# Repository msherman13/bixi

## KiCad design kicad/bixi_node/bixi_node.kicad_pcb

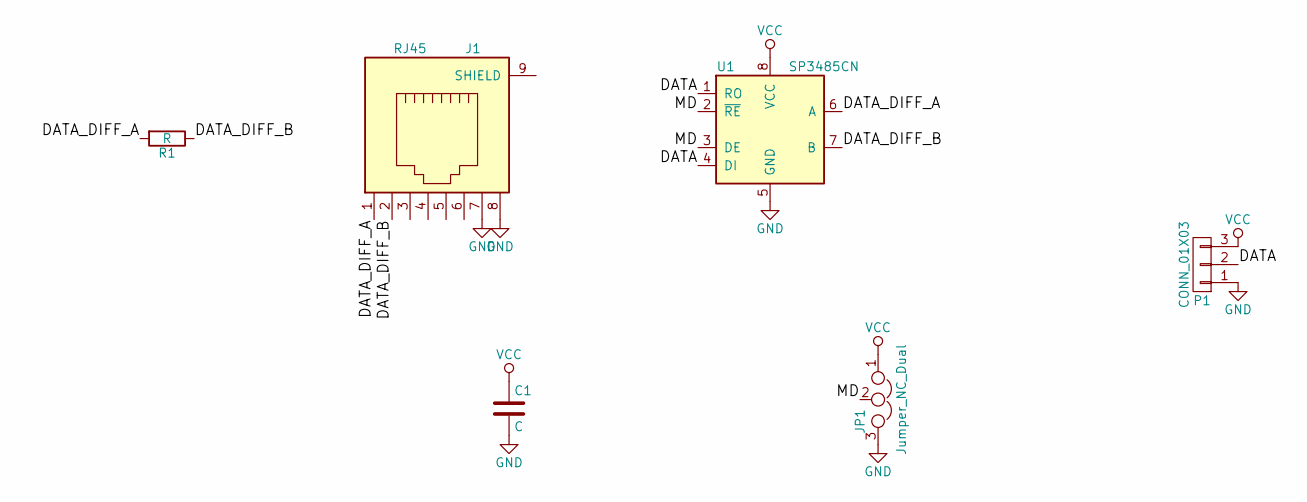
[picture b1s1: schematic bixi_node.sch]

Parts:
C1: C; C_Axial_L3.8mm_D2.6mm_P7.50mm_Horizontal
J1: RJ45; RJ45_8
JP1: Jumper_NC_Dual; jumper_3_pin_fixed
P1: CONN_01X03; 3-wire-hole-with-relief
R1: R; Resistor_Horizontal_RM7mm
U1: SP3485CN; DIP-8_W7.62mm

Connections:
/DATA: P1.2, U1.1 (RO), U1.4 (DI)
/DATA_DIFF_A: J1.1, R1.2, U1.6 (A)
/DATA_DIFF_B: J1.2, R1.1, U1.7 (B)
/MD: JP1.2, U1.2 (~RE~), U1.3 (DE)
GND: C1.2, J1.7, J1.8, JP1.3, P1.1, U1.5 (GND)
VCC: C1.1, JP1.1, P1.3, U1.8 (VCC)

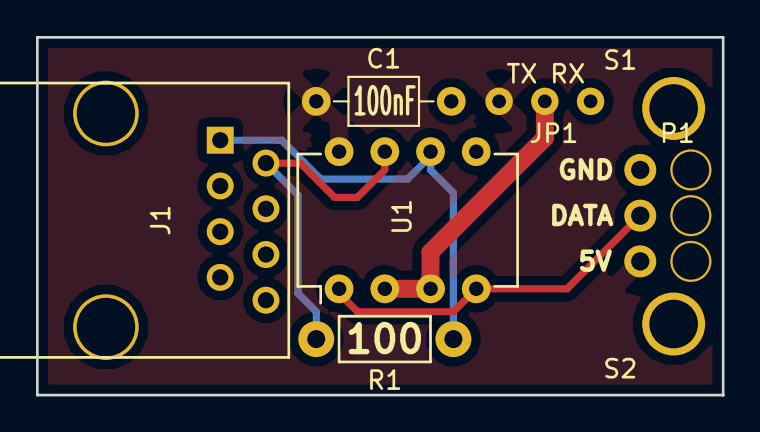
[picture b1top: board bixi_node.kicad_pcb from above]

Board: 2 copper layers, 38.1 x 19.9 mm, 8 parts (0 on the bottom side), 6 nets.

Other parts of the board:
S1, S2: MountingHole_2.7mm_Pad

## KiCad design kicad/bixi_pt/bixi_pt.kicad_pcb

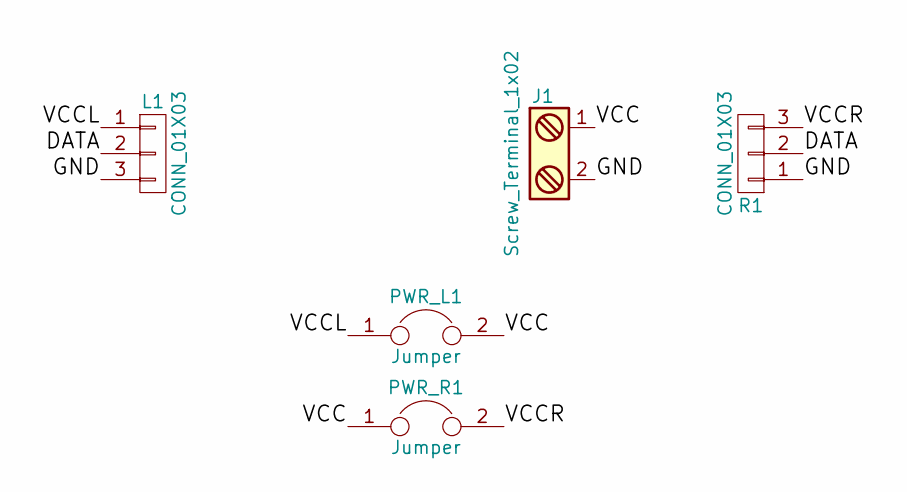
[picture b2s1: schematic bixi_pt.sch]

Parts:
J1: Screw_Terminal_1x02; OSTYK42102030-2P-Terminal
L1: CONN_01X03; 3-wire-hole-with-relief
PWR_L1: Jumper; Pin_Header_Straight_1x02_Pitch2.54mm
PWR_R1: Jumper; Pin_Header_Straight_1x02_Pitch2.54mm
R1: CONN_01X03; 3-wire-hole-with-relief

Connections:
/DATA: L1.2, R1.2
/GND: J1.2, L1.3, R1.1
/VCC: J1.1, PWR_L1.2, PWR_R1.1
/VCCL: L1.1, PWR_L1.1
/VCCR: PWR_R1.2, R1.3

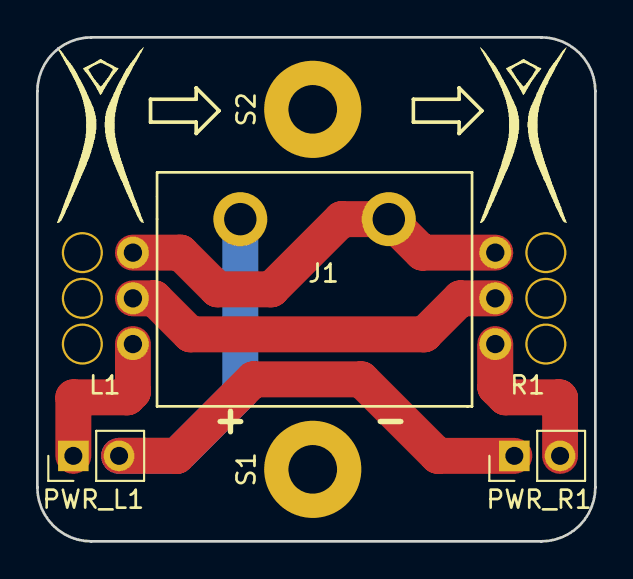
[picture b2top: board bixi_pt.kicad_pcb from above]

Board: 2 copper layers, 31.0 x 28.0 mm, 9 parts (0 on the bottom side), 5 nets.

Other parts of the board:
S1, S2: MountingHole_3.5mm; MountingHole_2.7mm_Pad
burner-logo: burner-logo-fs
burner-logo#2: burner-logo-fs

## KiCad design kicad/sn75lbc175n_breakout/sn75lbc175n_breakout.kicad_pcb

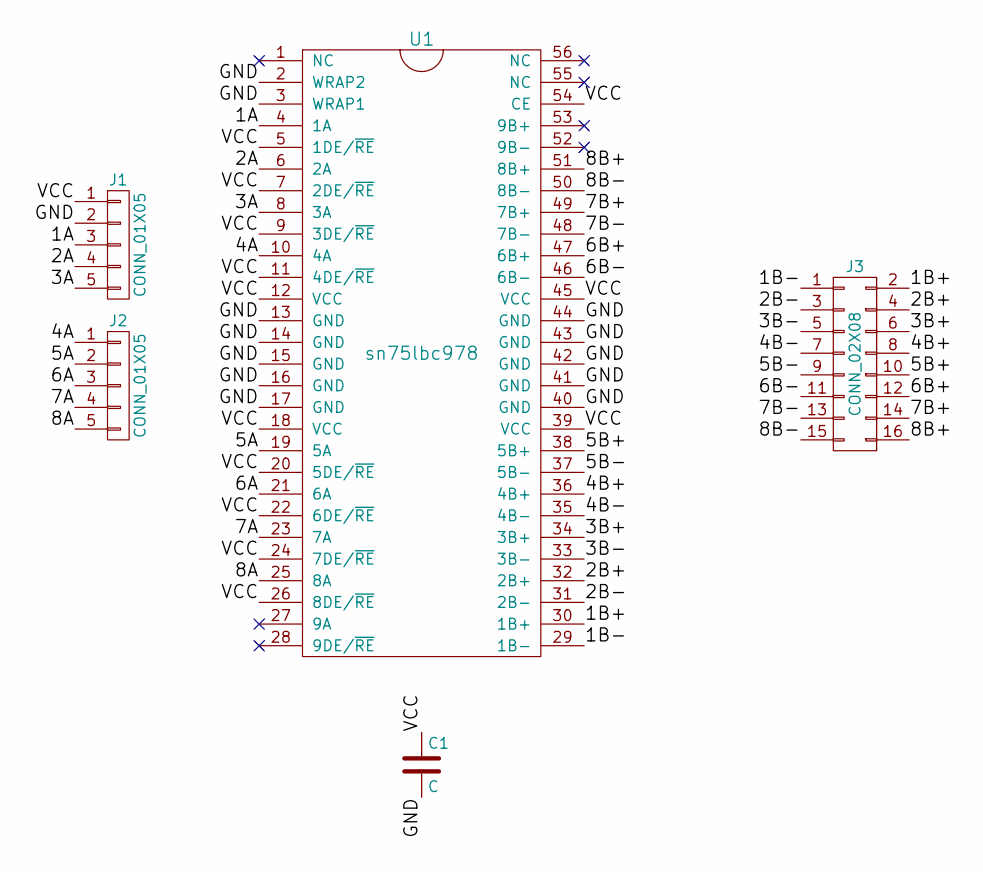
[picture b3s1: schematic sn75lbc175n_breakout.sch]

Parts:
C1: C; C_Disc_D4.7mm_W2.5mm_P5.00mm
J1, J2: CONN_01X05; Pin_Header_Straight_1x05_Pitch2.54mm
J3: CONN_02X08; Pin_Header_Straight_2x08_Pitch2.54mm
U1: sn75lbc978; SSOP-56_7.5x18.5mm_Pitch0.635mm

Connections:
/1A: J1.3, U1.4 (1A)
/1B+: J3.2, U1.30 (1B+)
/1B-: J3.1, U1.29 (1B-)
/2A: J1.4, U1.6 (2A)
/2B+: J3.4, U1.32 (2B+)
/2B-: J3.3, U1.31 (2B-)
/3A: J1.5, U1.8 (3A)
/3B+: J3.6, U1.34 (3B+)
/3B-: J3.5, U1.33 (3B-)
/4A: J2.1, U1.10 (4A)
/4B+: J3.8, U1.36 (4B+)
/4B-: J3.7, U1.35 (4B-)
/5A: J2.2, U1.19 (5A)
/5B+: J3.10, U1.38 (5B+)
/5B-: J3.9, U1.37 (5B-)
/6A: J2.3, U1.21 (6A)
/6B+: J3.12, U1.47 (6B+)
/6B-: J3.11, U1.46 (6B-)
/7A: J2.4, U1.23 (7A)
/7B+: J3.14, U1.49 (7B+)
/7B-: J3.13, U1.48 (7B-)
/8A: J2.5, U1.25 (8A)
/8B+: J3.16, U1.51 (8B+)
/8B-: J3.15, U1.50 (8B-)
/GND: C1.2, J1.2, U1.2 (WRAP2), U1.3 (WRAP1), U1.13 (GND), U1.14 (GND), U1.15 (GND), U1.16 (GND), U1.17 (GND), U1.40 (GND), U1.41 (GND), U1.42 (GND), U1.43 (GND), U1.44 (GND)
/VCC: C1.1, J1.1, U1.5 (1DE/~RE), U1.7 (2DE/~RE), U1.9 (3DE/~RE), U1.11 (4DE/~RE), U1.12 (VCC), U1.18 (VCC), U1.20 (5DE/~RE), U1.22 (6DE/~RE), U1.24 (7DE/~RE), U1.26 (8DE/~RE), U1.39 (VCC), U1.45 (VCC), U1.54 (CE)

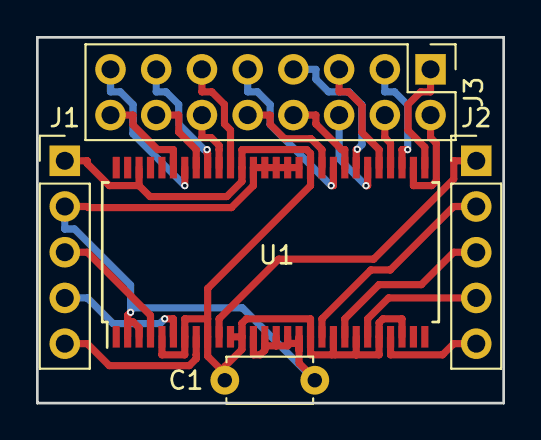
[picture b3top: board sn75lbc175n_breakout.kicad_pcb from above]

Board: 2 copper layers, 25.9 x 20.3 mm, 5 parts (0 on the bottom side), 26 nets.

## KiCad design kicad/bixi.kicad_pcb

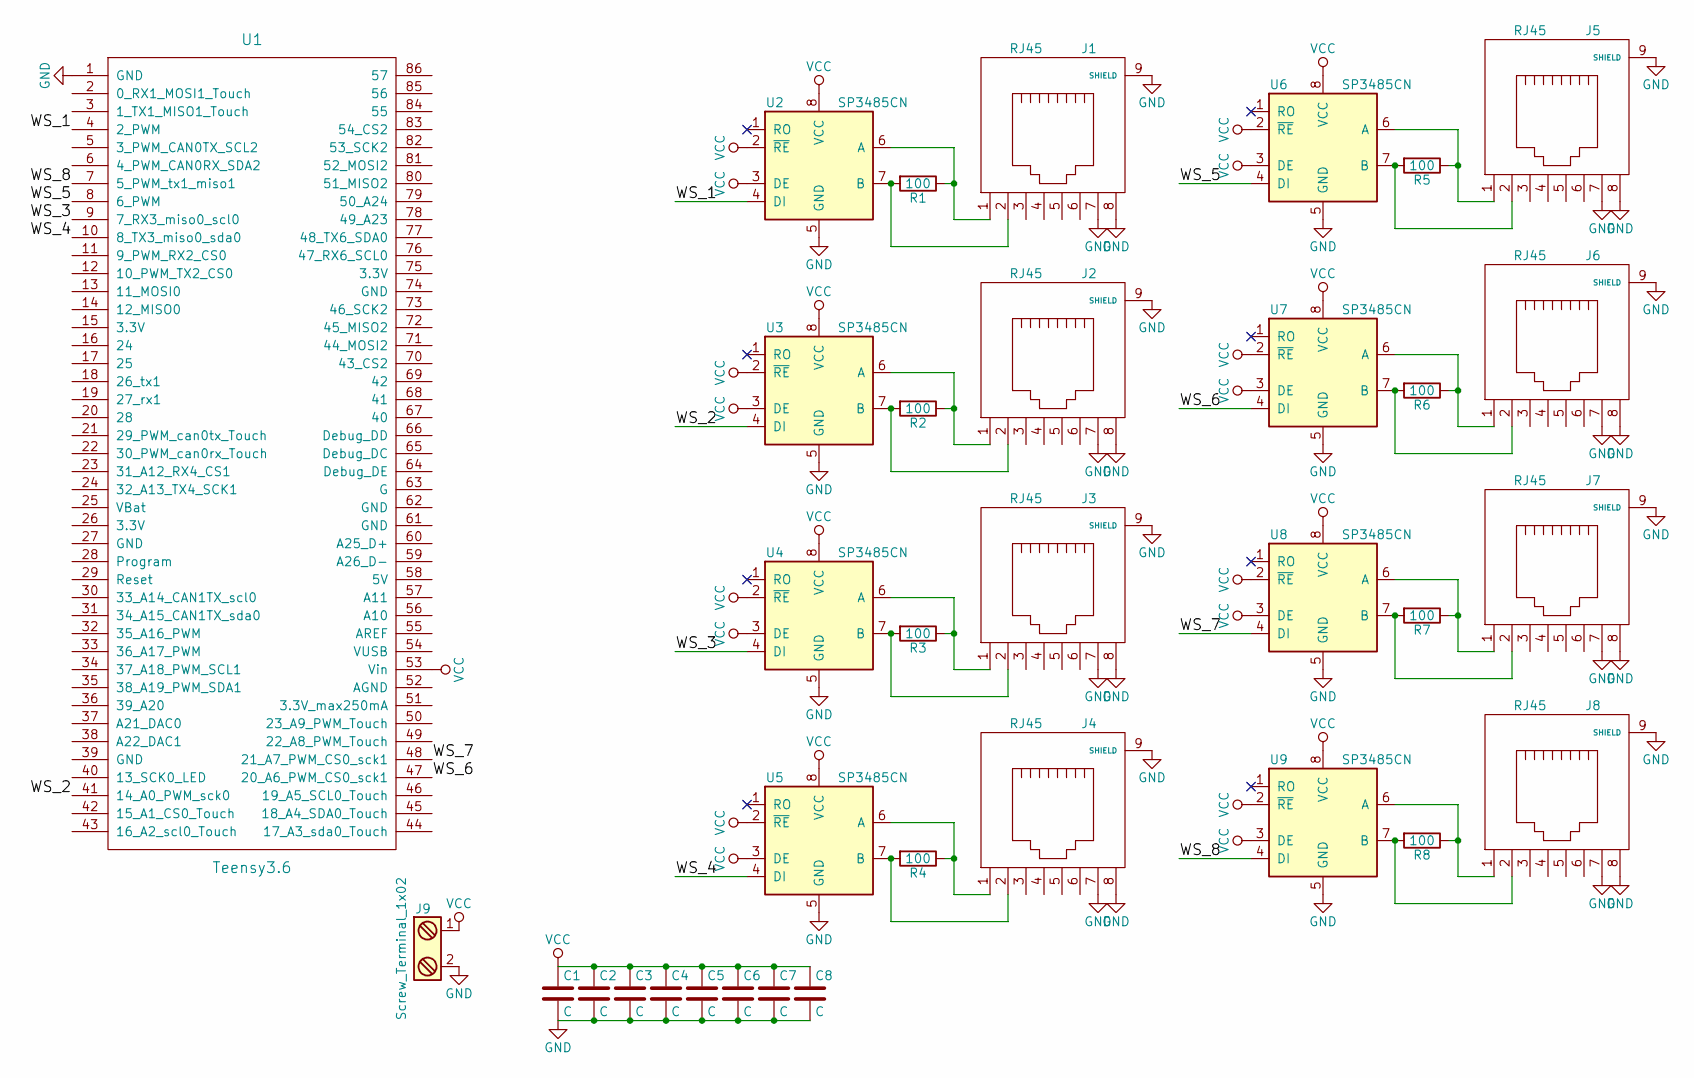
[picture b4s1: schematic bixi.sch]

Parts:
C1, C2, C3, C4, C5, C6, C7, C8: C; C_Disc_D3_P2.5
J1, J2, J3, J4, J5, J6, J7, J8: RJ45; RJ45_8
J9: Screw_Terminal_1x02; HB9500-2P
R1, R2, R3, R4, R5, R6, R7, R8: 100; Resistor_Horizontal_RM7mm
U1: Teensy3.6; Teensy35_36
U2, U3, U4, U5, U6, U7, U8, U9: SP3485CN; DIP-8_W7.62mm

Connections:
/WS_1: U1.4 (2_PWM), U2.4 (DI)
/WS_2: U1.41 (14_A0_PWM_sck0), U3.4 (DI)
/WS_3: U1.9 (7_RX3_miso0_scl0), U4.4 (DI)
/WS_4: U1.10 (8_TX3_miso0_sda0), U5.4 (DI)
/WS_5: U1.8 (6_PWM), U6.4 (DI)
/WS_6: U1.47 (20_A6_PWM_CS0_sck1), U7.4 (DI)
/WS_7: U1.48 (21_A7_PWM_CS0_sck1), U8.4 (DI)
/WS_8: U1.7 (5_PWM_tx1_miso1), U9.4 (DI)
GND: C1.2, C2.2, C3.2, C4.2, C5.2, C6.2, C7.2, C8.2, J1.7, J1.8, J1.9 (SHIELD), J2.7, J2.8, J2.9 (SHIELD), J3.7, J3.8, J3.9 (SHIELD), J4.7, J4.8, J4.9 (SHIELD), J5.7, J5.8, J5.9 (SHIELD), J6.7, J6.8, J6.9 (SHIELD), J7.7, J7.8, J7.9 (SHIELD), J8.7, J8.8, J8.9 (SHIELD), J9.2, U1.1 (GND), U2.5 (GND), U3.5 (GND), U4.5 (GND), U5.5 (GND), U6.5 (GND), U7.5 (GND), U8.5 (GND), U9.5 (GND); also elsewhere on the board
unnamed: J1.1, R1.1, U2.6 (A)
unnamed: J1.2, R1.2, U2.7 (B)
unnamed: J2.1, R2.1, U3.6 (A)
unnamed: J2.2, R2.2, U3.7 (B)
unnamed: J3.1, R3.1, U4.6 (A)
unnamed: J3.2, R3.2, U4.7 (B)
unnamed: J4.1, R4.1, U5.6 (A)
unnamed: J4.2, R4.2, U5.7 (B)
unnamed: J5.1, R5.1, U6.6 (A)
unnamed: J5.2, R5.2, U6.7 (B)
unnamed: J6.1, R6.1, U7.6 (A)
unnamed: J6.2, R6.2, U7.7 (B)
unnamed: J7.1, R7.1, U8.6 (A)
unnamed: J7.2, R7.2, U8.7 (B)
unnamed: J8.1, R8.1, U9.6 (A)
unnamed: J8.2, R8.2, U9.7 (B)
VCC: C1.1, C2.1, C3.1, C4.1, C5.1, C6.1, C7.1, C8.1, J9.1, U1.53 (Vin), U2.2 (~RE~), U2.3 (DE), U2.8 (VCC), U3.2 (~RE~), U3.3 (DE), U3.8 (VCC), U4.2 (~RE~), U4.3 (DE), U4.8 (VCC), U5.2 (~RE~), U5.3 (DE), U5.8 (VCC), U6.2 (~RE~), U6.3 (DE), U6.8 (VCC), U7.2 (~RE~), U7.3 (DE), U7.8 (VCC), U8.2 (~RE~), U8.3 (DE), U8.8 (VCC), U9.2 (~RE~), U9.3 (DE), U9.8 (VCC)

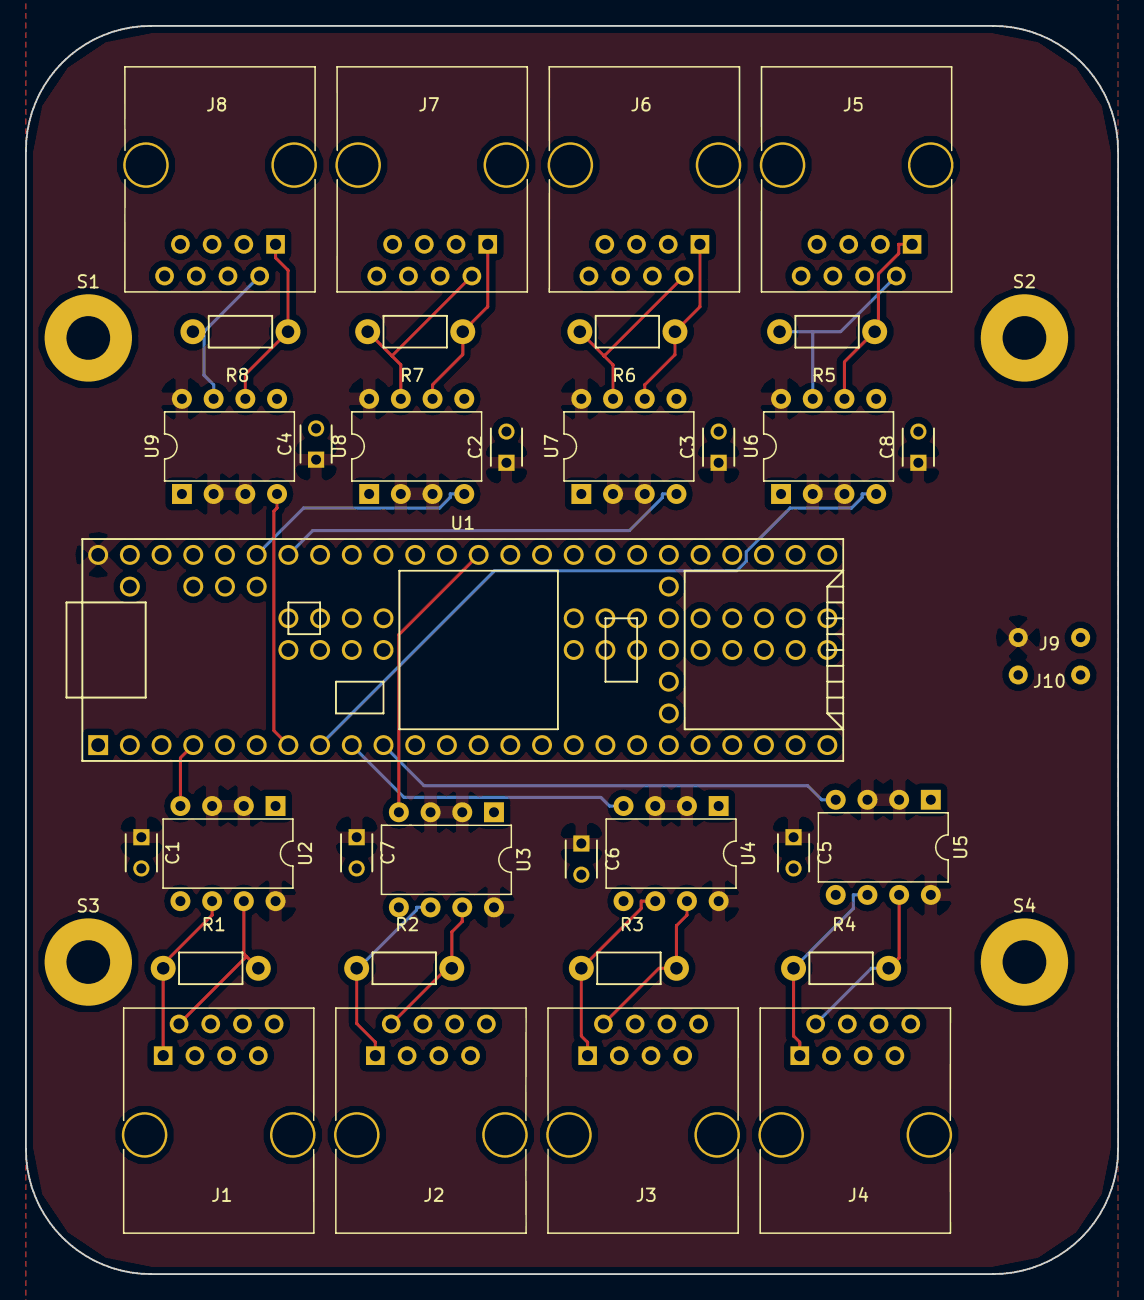
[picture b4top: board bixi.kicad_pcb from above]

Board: 2 copper layers, 87.5 x 100.0 mm, 40 parts (0 on the bottom side), 26 nets.

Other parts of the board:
J10: Screw_Terminal_1x01; A116169CT_SPADE_CONNECTOR
S1, S2, S3, S4: MountingHole_3.5mm_Pad
bm_streets: bm_streets

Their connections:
GND: J10.1; also elsewhere on the board

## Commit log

2017-01-22 makefile, example neopixel driver
2017-02-12 initial routines working. out of memory on arduino nano
2017-03-04 style fixes, fix to HoldRainbow hue wraparound
2017-03-04 support for driving strips on multiple pins
2017-03-04 fixed exitRoutine bug, removed debug logging
2017-03-18 Parallel output via FastLED; RoutineGrow
2017-03-18 initial kicad draft
2017-03-19 kicad schematic and layout
2017-03-19 updated controller layout
2017-03-19 more controller layout changes
2017-03-26 controller and receiver boards almost done for v1
2017-04-02 controller board screw terminal, screw holes. ready for build
2017-04-02 keep-out area for terminal block, finalized node pcb
2017-04-02 larger pads on screw terminal connector
2017-04-09 both pcb's sent to fab
2017-04-09 fix to silkscreen placement on bixi pcb
2017-04-16 bixi dome dimensions image
2017-04-25 v2 pcb
2017-04-29 bixi node updates
2017-04-30 v3 pcb first pass
2017-04-30 ignore swap files
2017-04-30 adding paul's repo as a submodule
2017-04-30 initial work on laying out the LED's on the frame
2017-05-02 v3 boards almost complete. added xcvr breakout, passthrough boards
2017-05-04 v3 pcb's plotted, ready for fab
2017-05-06 indices changes
2017-05-06 midway through addressing layer
2017-05-12 first changes for v4 pcb's
2017-05-12 remove std::string (not supported by arduino)
2017-05-13 initial work on pure c++ version
2017-05-13 sim is functional
2017-05-13 run sim in fake clock domain
2017-05-16 syntax
2017-05-16 move main.cpp into emulator files
2017-05-16 first piece of PixelArray re-write
2017-05-16 FastLED: Fix issue with driver on short strands
2017-05-16 PixelArray takes external array as reference
2017-05-17 plain implementation is functional
2017-05-17 dimensions2, first hex routine
2017-05-19 DoubleHex, bidirectional plains, color pallete
2017-05-20 rgb2hsv conversion for sim is compiling, probably doesnt work
2017-05-20 polygon, routines owned by pixel array
2017-05-20 RoutineGlare
2017-05-20 initial work on routine-sticks
2017-05-21 added missing file
2017-05-21 new power injection board is ready
2017-05-21 new controller board
2017-05-21 fixes to boards, node still in progress
2017-05-21 RoutineSticks, RoutineCrawl working
2017-05-22 CDome, fixes to swipe routine
2017-05-23 updated controller board with stacked rj45
2017-05-23 re-plotted controller board after DRC
2017-05-24 node work for keystone box
2017-05-24 final v4 pcb's, sent to production
2017-05-29 routine fire work
2017-05-29 quickcg skeleton
2017-05-29 some cleanup
2017-06-03 fix a bug introduced in the previous commit
2017-06-03 more bug fixes, fixed memory leak
2017-06-03 Consolidated pixel array constructors, dome mappings
2017-06-03 initial work on routine balls, raster grid
2017-06-03 routine balls is functional
2017-06-04 everything functional, first work on 2d routine
2017-06-04 some changes
2017-06-04 map projections seem to be functional, needs testing
2017-06-04 lambert conformal projection seems functional
2017-06-04 lambert map projection is fully functional
2017-06-04 removed CompleteConfig, kills memory. use external override instead
2017-06-04 move pixelarrays to static memory pool
2017-06-05 fixed the memory allocation nightmare. everything statically allocated
2017-06-06 Split out pixel array with legs to derived class
2017-06-06 shutdown interface in CRoutine, RoutineBall shutdown, NoTech implementation
2017-06-06 fixup of dome for shutdown routine
2017-06-06 fix to dome, routineBall shutdown
2017-06-10 fade-in transitions are functional
2017-06-11 RoutineRain looks good
2017-06-11 fix include in balls
2017-06-11 rough dimensions for dome, generation scripts
2017-06-11 remove debug logging
2017-06-11 checking in
2017-06-11 fixes for refresh rate, addressing issue
2017-06-11 make Dome leg-based
2017-06-11 Dome shape constructors
2017-06-15 everything working except make issue with teensy
2017-06-16 new layout, routine-spin, fixed point math
2017-06-18 fix map corners
2017-06-20 new dimensions from sketchup, mapprojection is broken
2017-06-21 fixed lambert projection (was using std::abs instead of fabs)
2017-06-21 OCTO2813 dma
2017-06-21 routinespin is faster
2017-06-21 octo emulator
2017-06-21 linker
2017-06-21 missing file
2017-06-21 initial version working. need to move map projection to pre-processor
2017-06-22 map projection in pre-processor
2017-06-24 dome and power maps
2017-06-24 dome and power map pdf's
2017-06-24 lots of progress
2017-06-24 transition out instead of transition in
2017-06-24 remove glare from dome for now
2017-06-25 LegsAndNeck is functional
2017-06-25 fixed arduino make
2017-06-25 head is functional
2017-06-25 fire is still kinda broken`
2017-06-27 some work on color correction
2017-07-15 add 3 led's to every dome dimension
2017-07-19 bug fix in 3d_locations_from_sketchup file
2017-07-19 turn off gamma correction, fix issue with uninitialized CRGB values
2017-07-20 fix a bug which allows Dome to go into RoutineIdle
2017-07-20 fix for Math::fast_pow which caused nan to be returned
2017-07-20 reduce qty of balls, increase gamma
2017-07-20 swipe screen transition
2017-07-21 some optimizations to transition routines
2017-07-21 RoutineRubics
2017-07-23 RoutineTest, instantiated in CDome
2017-07-23 rename dome mappings csv
2017-07-23 move file
2017-07-23 automate legs and neck mapping
2017-07-23 Head mappings now automated
2017-07-23 dome shape map, inventory spreadsheet
2017-07-25 mac build support
2017-07-29 bugfix in leg mappings, traversenose routine for head
2017-07-29 remove debug printf
2017-07-29 shape routines for dome
2017-07-30 routine sparkle is ready
2017-07-30 fade out on crawl routine
2017-07-31 add sparkle background to crawl
2017-07-31 routine stars partially working
2017-07-31 routine stars is done
2017-08-01 make routine-stars per-shape on dome
2017-08-01 reduce allocation qty for sparkle and stars
2017-08-01 new head_mappings.csv from Kyle's measurements
2017-08-01 dome first routine is stars
2017-08-01 constexpr for dome initial routine
2017-08-01 new colors, routine-attack
2017-08-01 dome test per shape
2017-08-02 fixes
2017-08-02 fix MAJOR bug with FastLED initialization scheme
2017-08-03 RoutineTurn, dome support for sparkle and sparkle colors
2017-08-05 Add border to rubics swipe
2017-08-05 initial work on expand routine
2017-08-05 RoutineExpand is functional
2017-08-06 some dome fixes
2017-08-06 head mapping updates from dixon
2017-08-06 initial fixes to head
2017-08-07 revert head tests
2017-08-07 finished head mapping
2017-08-07 comment routine-expand
2017-08-07 updated neck indices
2017-08-07 remove expand from dome
2017-08-07 dome fix
2017-08-13 cyclepallete only use 2 colors
2017-08-13 add solid routine to dome
2017-08-20 nose is done
2017-08-20 head is done
2017-08-20 legs and neck done
2017-08-20 traverse nose toggle on vs off
2017-08-20 remove sparkle from legs/neck
